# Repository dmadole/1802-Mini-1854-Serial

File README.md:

# 1802-Mini-1854-Serial
This is the 1854 UART serial card for the [1802/Mini](https://github.com/dmadole/1802-Mini) system. It supports the following features:

* Sixteen baud rates from 300 to 57600
* Jumpers to determine default baud rate at reset
* Baud rate can be changed by software
* No rare chips except the CDP1854 itself
* Supports group I/O port expansion
* Jumper-selected address 2/3, 4/5, or 6/7
* Jumper-selected interrupt poll bit on EF1-EF4
* Supports input flow control using software-driven bit
* Supports output flow control using software-read ES pin
* Jumper-selected transmit and receive interrupts or only for receive
* Both DCE (female) and DTE (male) 9-pin ports, populate either or both
* A TTL-level port with “standard” FTDI-type USB cable pinout

Gerber files for the PCBs and PDF schematics can be found in [Releases](https://github.com/dmadole/1802-Mini-1854-Serial/releases).

BOMS and any applicable errata or other notes can be found in [notes](https://github.com/dmadole/1802-Mini-1854-Serial/tree/main/notes).

For availability of kits and bare PCBs please see http://madole.net/1802/mini/kits

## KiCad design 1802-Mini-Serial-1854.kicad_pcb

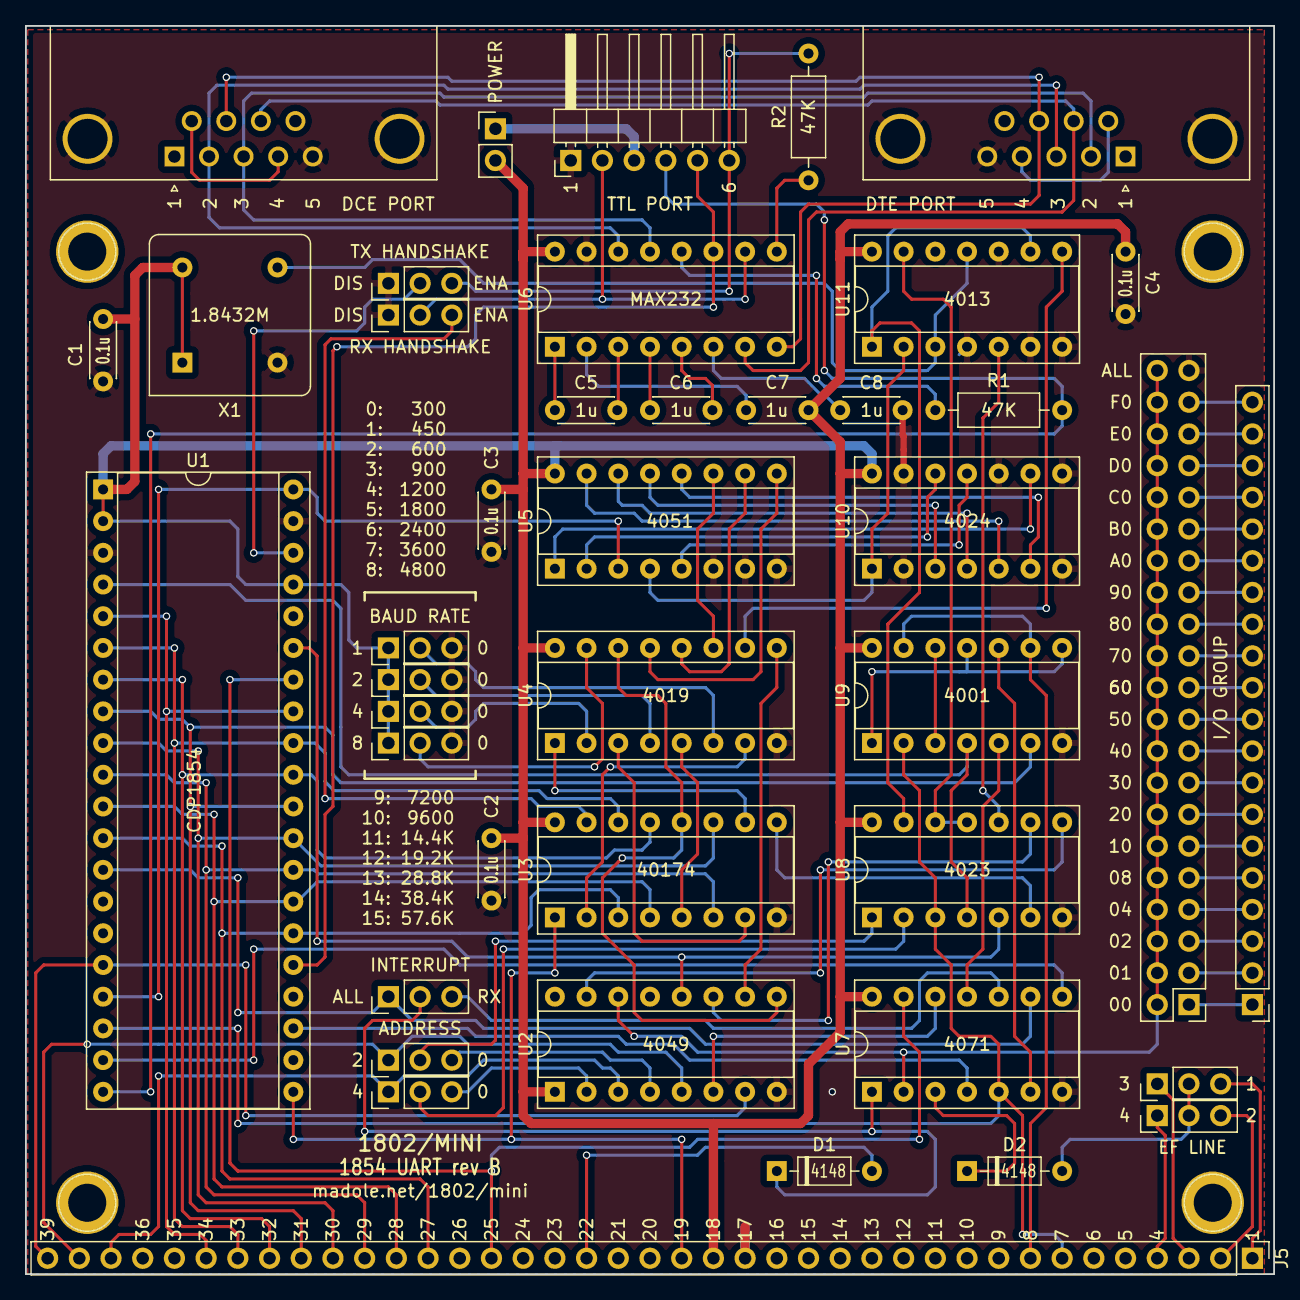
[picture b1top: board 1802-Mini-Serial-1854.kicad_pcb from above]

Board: 2 copper layers, 100.0 x 100.0 mm, 46 parts (0 on the bottom side), 112 nets.

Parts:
C1, C2, C3, C4: 0.1u; C_Disc_D4.3mm_W1.9mm_P5.00mm
C5, C6, C7, C8: 1uF; C_Disc_D4.3mm_W1.9mm_P5.00mm
D1, D2: 4148; D_DO-35_SOD27_P7.62mm_Horizontal
J1, J2, J3, J4: Mount; 1pin
J5: Expansion; PinHeader_1x39_P2.54mm_Vertical
J6: GRP_EXP; PinHeader_1x20_P2.54mm_Vertical
J7: GRP_SEL; PinHeader_2x21_P2.54mm_Vertical
J8: DCE; DSUB-9_Female_Horizontal_P2.77x2.84mm_EdgePinOffset7.70mm_H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
J9: DTE; DSUB-9_Male_Horizontal_P2.77x2.84mm_EdgePinOffset7.70mm_Hou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
J10: TTL; PinHeader_1x06_P2.54mm_Horizontal
JP1: N2; PinHeader_1x03_P2.54mm_Vertical
JP2: RX_HSHK; PinHeader_1x03_P2.54mm_Vertical
JP3: EF1/3; PinHeader_1x03_P2.54mm_Vertical
JP4: EF2/4; PinHeader_1x03_P2.54mm_Vertical
JP5: TX_HSHK; PinHeader_1x03_P2.54mm_Vertical
JP6: BR8; PinHeader_1x03_P2.54mm_Vertical
JP7: BR4; PinHeader_1x03_P2.54mm_Vertical
JP8: BR2; PinHeader_1x03_P2.54mm_Vertical
JP9: BR1; PinHeader_1x03_P2.54mm_Vertical
JP10: INT_SRC; PinHeader_1x03_P2.54mm_Vertical
JP11: Jumper_2_Open; PinHeader_1x02_P2.54mm_Vertical
JP13: N1; PinHeader_1x03_P2.54mm_Vertical
R1, R2: R; R_Axial_DIN0207_L6.3mm_D2.5mm_P10.16mm_Horizontal
U1: CDP1854; DIP-40_W15.24mm_Socket
U2: 4049; DIP-16_W7.62mm_Socket
U3: 74LS174; DIP-16_W7.62mm_Socket
U4: 4019; DIP-16_W7.62mm_Socket
U5: 4051; DIP-16_W7.62mm_Socket
U6: MAX232; DIP-16_W7.62mm_Socket
U7: 4071; DIP-14_W7.62mm_Socket
U8: 4023; DIP-14_W7.62mm_Socket
U9: 4001; DIP-14_W7.62mm_Socket
U10: 4024; DIP-14_W7.62mm_Socket
U11: 4013; DIP-14_W7.62mm_Socket
X1: 1.8432; Oscillator_DIP-8

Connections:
/BUS0: J5.27, U1.12, U1.26, U3.3
/BUS1: J5.28, U1.11, U1.27, U3.4
/BUS2: J5.29, U1.10, U1.28, U3.6
/BUS3: J5.30, U1.9, U1.29, U3.11
/BUS5: J5.32, U1.7, U1.31, U3.13
/BUS6: J5.33, U1.6, U1.32, U3.14
/BUS7: J5.34, U1.5, U1.33
BUS4: J5.31, U1.8, U1.30, U9.6
CS1: U1.23, U7.4
CS3: U1.35, U2.12, U8.5
GND: C1.2, C2.2, C3.2, C4.2, C8.2, J5.17, J7.41, J8.0, J8.5, J9.0, J9.5, J10.1, JP2.1, JP5.1, JP6.3, JP7.3, JP8.3, JP9.3, U1.3, U1.39, U2.8, U3.8, U4.8, U5.6, U5.7, U5.8, U6.15, U7.7, U8.7, U9.7, U10.2, U10.7, U10.8, U10.10, U10.13, U11.4, U11.6, U11.7, U11.10, X1.4
LATCH: U3.9, U8.6
N0: J5.39, U1.16, U2.7
N1: J5.38, JP13.1, U2.5
N2: J5.37, JP1.1, U2.3
unnamed: C5.1, U6.1
unnamed: C5.2, U6.3
unnamed: C6.1, U6.4
unnamed: C6.2, U6.5
unnamed: C7.2, U6.2
unnamed: C8.1, U6.6
unnamed: D1.1, JP10.2, U7.1
unnamed: D2.1, U7.3
unnamed: D2.2, JP3.2, JP4.2
unnamed: J6.1, J7.1
unnamed: J6.2, J7.3
unnamed: J6.3, J7.5
unnamed: J6.4, J7.7
unnamed: J6.5, J7.9
unnamed: J6.6, J7.11
unnamed: J6.7, J7.13
unnamed: J6.8, J7.15
unnamed: J6.9, J7.17
unnamed: J6.10, J7.19
unnamed: J6.11, J7.21
unnamed: J6.12, J7.23
unnamed: J6.13, J7.25
unnamed: J6.14, J7.27
unnamed: J6.15, J7.29
unnamed: J6.16, J7.31
unnamed: J6.17, J7.33
unnamed: J6.18, J7.35
unnamed: J6.19, J7.37
unnamed: J6.20, J7.39
unnamed: J8.2, J9.3, U6.14
unnamed: J8.3, J9.2, U6.13
unnamed: J8.4, J8.6
unnamed: J8.7, J9.8, U6.8
unnamed: J8.8, J9.7, U6.7
unnamed: J9.4, J9.6
unnamed: J10.2, JP5.2, U6.10
unnamed: J10.3, JP11.1
unnamed: J10.4, R1.2, U1.20
unnamed: J10.5, U1.25, U6.11
unnamed: J10.6, JP2.3, R2.2
unnamed: JP1.2, U8.2
unnamed: JP1.3, U2.2
unnamed: JP2.2, U1.38
unnamed: JP5.3, U3.15
unnamed: JP6.2, U4.15
unnamed: JP7.2, U4.2
unnamed: JP8.2, U4.4
unnamed: JP9.2, U4.6
unnamed: JP10.3, U7.10
unnamed: JP13.2, U8.1
unnamed: JP13.3, U2.4
unnamed: R1.1, U6.12
unnamed: R2.1, U6.9
unnamed: U1.17, U1.40, U5.3
unnamed: U2.6, U7.12
unnamed: U2.9, U3.12, U4.14
unnamed: U2.10, U4.9
unnamed: U2.11, U8.9
unnamed: U2.15, U8.8
unnamed: U3.2, U4.7
unnamed: U3.5, U4.5
unnamed: U3.7, U4.3
unnamed: U3.10, U4.1
unnamed: U4.11, U5.11
unnamed: U4.12, U5.10
unnamed: U4.13, U5.9
unnamed: U7.6, U9.10
unnamed: U7.11, U9.5
unnamed: U9.1, U9.8, U9.11
unnamed: U9.3, U9.12
unnamed: U5.4, U10.1, U11.2
unnamed: U5.13, U10.3
unnamed: U5.14, U10.4
unnamed: U5.15, U10.5
unnamed: U5.12, U10.6
unnamed: U5.1, U10.9
unnamed: U5.5, U10.11
unnamed: U5.2, U10.12
unnamed: U8.13, U11.1, U11.9
unnamed: U8.10, U11.5
unnamed: U4.10, U11.8
unnamed: U11.3, U11.11, X1.5
unnamed: U8.11, U8.12, U11.13
TPA: J5.8, U9.9, U9.13
TPB: J5.7, U1.18, U7.5, U8.3, U9.2
VCC: C1.1, C2.1, C3.1, C4.1, C7.1, J5.18, JP6.1, JP7.1, JP8.1, JP9.1, JP11.2, U1.1, U1.2, U1.37, U2.1, U3.16, U4.16, U5.16, U6.16, U7.14, U8.14, U9.14, U10.14, U11.14, X1.1, X1.8
~CLEAR: J5.19, U1.21, U3.1
~CS2: U1.4, U8.4, U9.4
~DA: U1.19, U7.8
~EF1: J5.1, JP3.3
~EF2: J5.2, JP4.3
~EF3: J5.3, JP3.1
~EF4: J5.4, JP4.1
~GROUP: J7.2, J7.4, J7.6, J7.8, J7.10, J7.12, J7.14, J7.16, J7.18, J7.20, J7.22, J7.24, J7.26, J7.28, J7.30, J7.32, J7.34, J7.36, J7.38, J7.40, J7.42, U2.14, U7.2
~INT: D1.2, J5.22
~MRD: J5.25, U1.34, U7.13
~UINT: JP10.1, U1.13, U7.9

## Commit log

2021-08-26 Fix EF flags
2021-08-27 Layout fixes
2021-09-07 Create README.md
    # 1802-Mini-Compact-Flash
    This is the 1854 UART card for the [1802/Mini](https://github.com/dmadole/1802-Mini) system. It supports the following features:
    * Sixteen baud rates from 300 to 57600
    * Jumpers to determine default baud rate at reset
    * Baud rate can be changed by software
    * No rare chips except the CDP1854 itself
2021-09-13 Initial version
